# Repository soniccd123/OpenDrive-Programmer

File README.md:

# OpenDrive-Programmer
A open hardware USB programmer for the OpenDrive flashcart

# Other projects of the same family
- OpenDrive Genesis: https://github.com/soniccd123/OpenDrive-Genesis
- OpenDrive Programmer firmware: https://github.com/soniccd123/OpenDrive-Programmer-firmware
- OpenDrive Editor: https://github.com/soniccd123/OpenDrive-Editor

# What can it do?
- Read or write OpenDrive flashcarts Flash memory and FeRAM,
- Backup commercial cartridges
- Backup and restore commercial cartridges save games

# Why?
Created this from my old project with repros, as challenge and for personal use. Decided to share the project for other to use and learn. Hope it is useful to somebody!

# Why two boards?
This is just and option for those who are not so skilled with a soldering iron. The design contained in the Bluepill folders can use both a standart BluePill development module or be built as a standalone unit. When using a BluePill, not so many components are necessary and almost any SMD component is needed to be soldered (just the two 74LVC245). The design in the Standalone folder is the one that i've been using and its been tested, should be exactly equal to the BluePill one, it just don't have the solder points for the headers needed to connect the BluePill.

# How to use
Assemble the PCB, all the files needed for producing the PCB and Bill of Materials are available here. After assembling connect a STLINK to the STLINK port and write the firmware (available here: https://github.com/soniccd123/OpenDrive-Programmer-firmware). After that it is ready to be connected to a PC, it will be shown as a serial port. Connect to it using the OpenDrive Editor software and happy playing.

# Documentation
- Programmer Technical documentation, a constant work, sugestions are welcome:https://docs.google.com/document/d/e/2PACX-1vRtMwSrP43Q_9yeqR024jhnHt7tN-bjPW5AL-o--7ggXnXnSzmwVzF4QqODWmXAdS4KnoAx6XXx5pVw/pub
- MX29L3211 Datasheet: http://www.wolfgangrobel.de/electronics/datasheets/eprom/MX29L3211.pdf
- FM1808 Datasheet: https://datasheet.octopart.com/FM1808-70-PG-Ramtron-datasheet-8328945.pdf
- 74LVC8T245 Datasheet: https://assets.nexperia.com/documents/data-sheet/74LVC_LVCH8T245.pdf

# Troubleshooting
Most of the problems I had were related to bad solder joints, check and recheck your solder joints, specially the STM32 joints, lots of instabilities that I had were caused by falty contacts with solder.

# Disclaimer
I'm not a professional hardware engineer, while this programmer was designed to be the safest possible to your flashcart, I'm not responsible for any damages done if used or built wrong. Also, revise the design always before building the PCB, I'm a amateur human and errors may have been commited. It you spot anything, hit me with a message and I will happily fix that. Also, any sugestions are welcome!

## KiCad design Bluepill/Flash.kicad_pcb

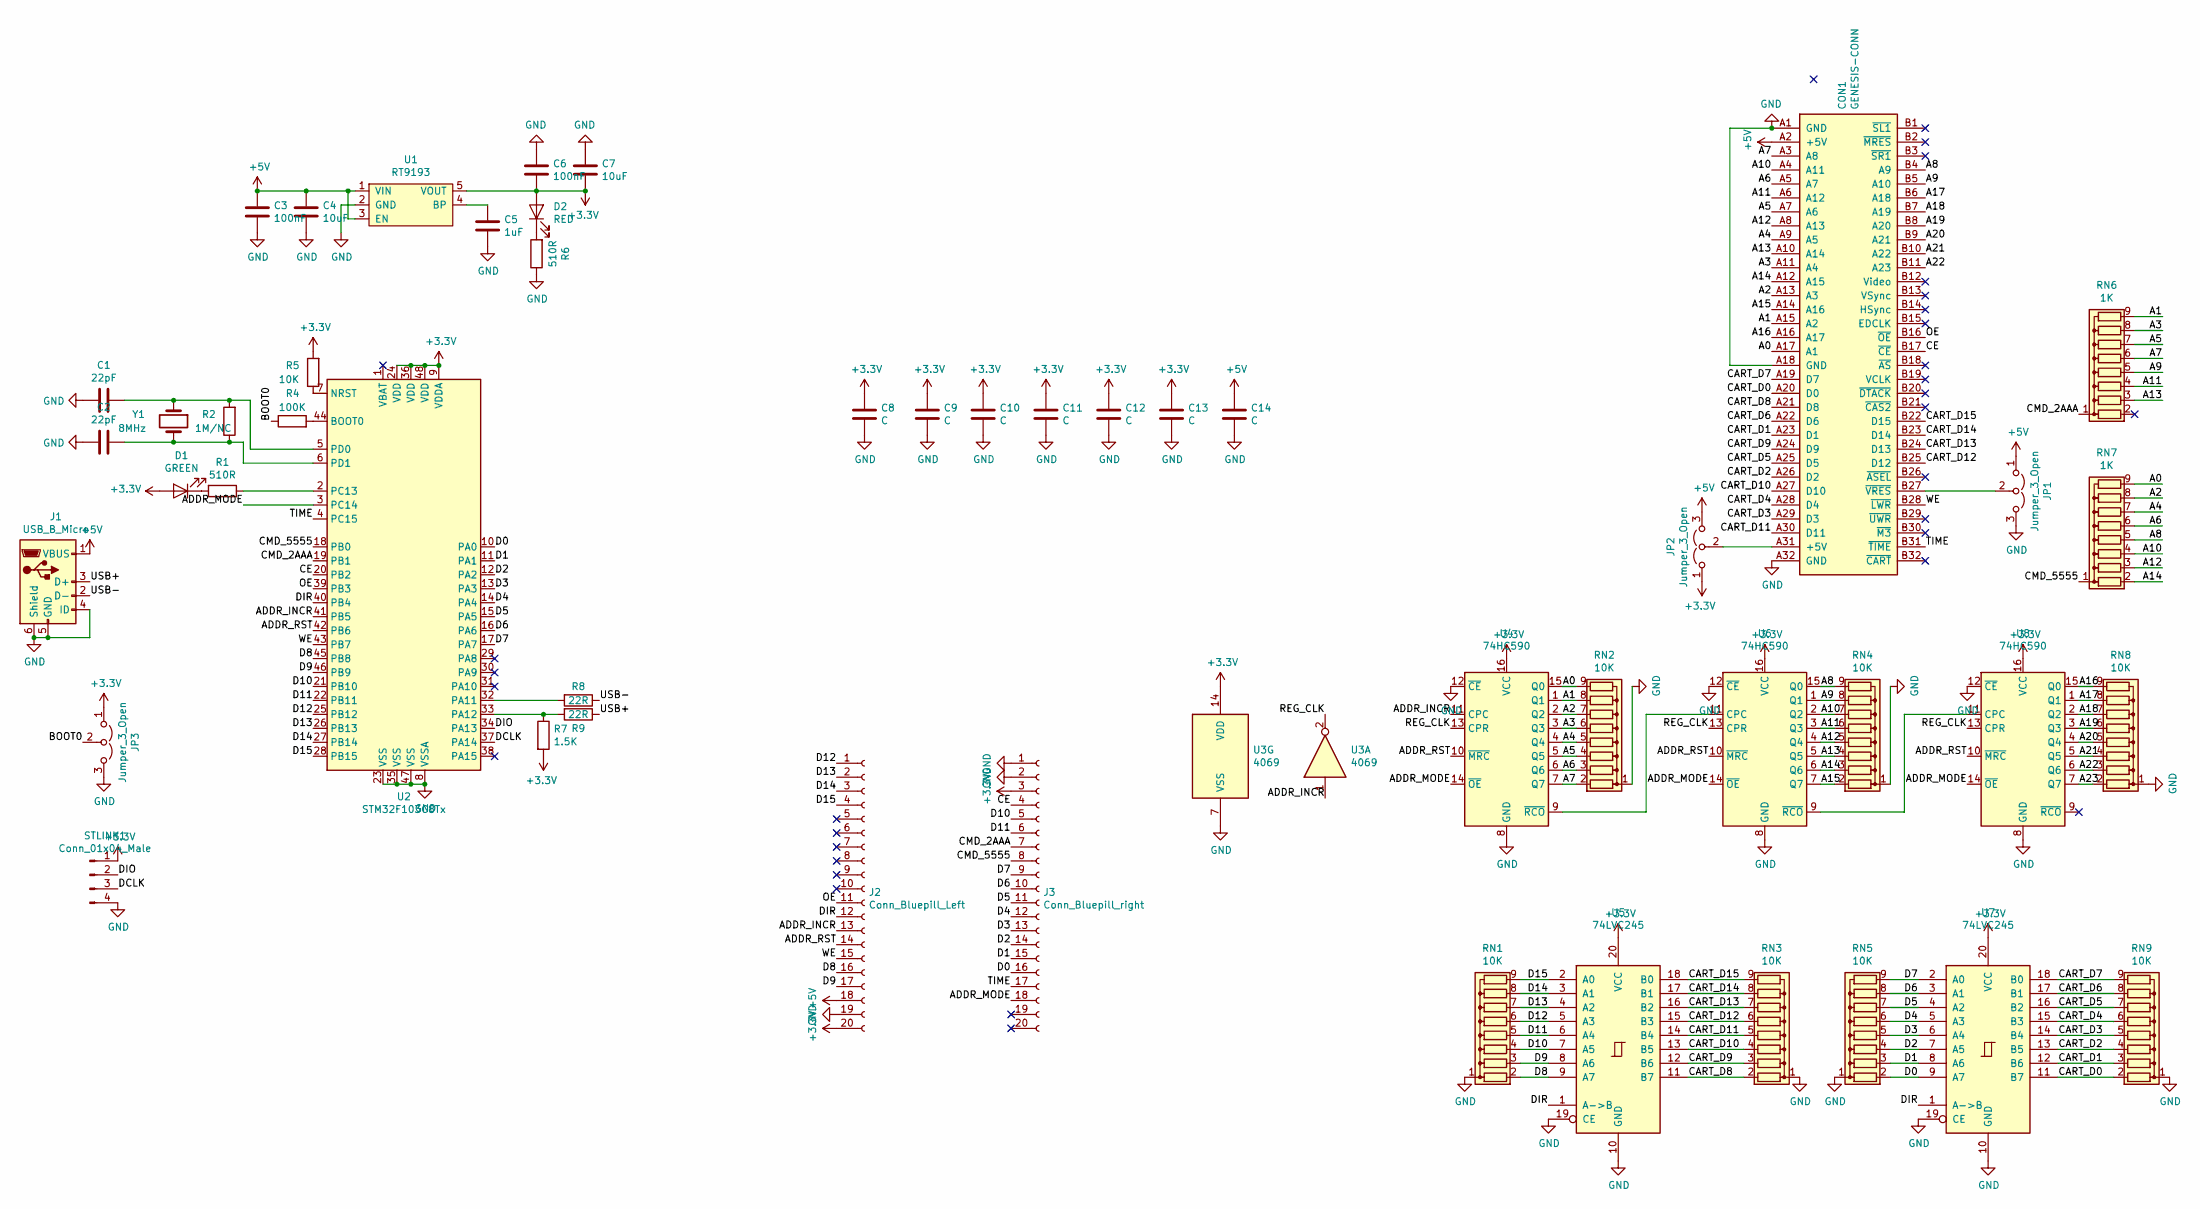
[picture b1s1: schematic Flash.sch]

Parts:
C1, C2: 22pF; C_0805_2012Metric_Pad1.15x1.40mm_HandSolder
C3, C6: 100nF; C_0805_2012Metric_Pad1.15x1.40mm_HandSolder
C4, C7: 10uF; C_0805_2012Metric_Pad1.15x1.40mm_HandSolder
C5: 1uF; C_0805_2012Metric_Pad1.15x1.40mm_HandSolder
C8, C9, C10, C11, C12, C13, C14: C; PinHeader_1x02_P2.54mm_Vertical
CON1: GENESIS-CONN; Digikey 1761469-1-ND
D1: GREEN; LED_D3.0mm
D2: RED; LED_D3.0mm
J1: USB_B_Micro; USB_Micro-B_Molex-105017-0001
J2: Conn_Bluepill_Left; PinSocket_1x20_P2.54mm_Vertical
J3: Conn_Bluepill_right; PinSocket_1x20_P2.54mm_Vertical
JP1, JP2, JP3: Jumper_3_Open; PinHeader_1x03_P2.54mm_Vertical
R1, R6: 510R; R_0805_2012Metric_Pad1.15x1.40mm_HandSolder
R2: 1M/NC; R_0805_2012Metric_Pad1.15x1.40mm_HandSolder
R4: 100K; R_0805_2012Metric_Pad1.15x1.40mm_HandSolder
R5: 10K; R_0805_2012Metric_Pad1.15x1.40mm_HandSolder
R7: 1.5K; R_0805_2012Metric_Pad1.15x1.40mm_HandSolder
R8, R9: 22R; R_0805_2012Metric_Pad1.15x1.40mm_HandSolder
RN1, RN2, RN3, RN4, RN5, RN8, RN9: 10K; R_Array_SIP9
RN6, RN7: 1K; R_Array_SIP9
STLINK1: Conn_01x04_Male; PinHeader_1x04_P2.54mm_Vertical
U1: RT9193; SOT-23-5_HandSoldering
U2: STM32F103C8Tx; LQFP-48_7x7mm_P0.5mm
U3: 4069; DIP-14_W7.62mm
U4, U6, U8: 74HC590; DIP-16_W7.62mm
U5, U7: 74LVC245; TSSOP-20_4.4x6.5mm_P0.65mm
Y1: 8MHz; Crystal_HC49-U_Vertical

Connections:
+3V3: C6.2, C7.2, C8.1, C9.1, C10.1, C11.1, C12.1, C13.1, D1.2 (A), D2.2 (A), J2.20, J3.3, JP2.1 (A), JP3.1 (A), R5.2, R7.2, STLINK1.1, U1.5 (VOUT), U2.9 (VDDA), U2.24 (VDD), U2.36 (VDD), U2.48 (VDD), U3.14 (VDD), U4.16 (VCC), U5.20 (VCC), U6.16 (VCC), U7.20 (VCC), U8.16 (VCC)
+5V: C3.1, C4.1, C14.1, CON1.A2 (+5V), J1.1 (VBUS), J2.18, JP1.1 (A), JP2.3 (B), U1.1 (VIN), U1.3 (EN)
/A0: CON1.A17 (A1), RN2.9 (R8), RN7.9 (R8), U4.15 (Q0)
/A1: CON1.A15 (A2), RN2.8 (R7), RN6.9 (R8), U4.1 (Q1)
/A2: CON1.A13 (A3), RN2.7 (R6), RN7.8 (R7), U4.2 (Q2)
/A3: CON1.A11 (A4), RN2.6 (R5), RN6.8 (R7), U4.3 (Q3)
/A4: CON1.A9 (A5), RN2.5 (R4), RN7.7 (R6), U4.4 (Q4)
/A5: CON1.A7 (A6), RN2.4 (R3), RN6.7 (R6), U4.5 (Q5)
/A6: CON1.A5 (A7), RN2.3 (R2), RN7.6 (R5), U4.6 (Q6)
/A7: CON1.A3 (A8), RN2.2 (R1), RN6.6 (R5), U4.7 (Q7)
/A8: CON1.B4 (A9), RN4.9 (R8), RN7.5 (R4), U6.15 (Q0)
/A9: CON1.B5 (A10), RN4.8 (R7), RN6.5 (R4), U6.1 (Q1)
/A10: CON1.A4 (A11), RN4.7 (R6), RN7.4 (R3), U6.2 (Q2)
/A11: CON1.A6 (A12), RN4.6 (R5), RN6.4 (R3), U6.3 (Q3)
/A12: CON1.A8 (A13), RN4.5 (R4), RN7.3 (R2), U6.4 (Q4)
/A13: CON1.A10 (A14), RN4.4 (R3), RN6.3 (R2), U6.5 (Q5)
/A14: CON1.A12 (A15), RN4.3 (R2), RN7.2 (R1), U6.6 (Q6)
/A15: CON1.A14 (A16), RN4.2 (R1), U6.7 (Q7)
/A16: CON1.A16 (A17), RN8.9 (R8), U8.15 (Q0)
/A17: CON1.B6 (A18), RN8.8 (R7), U8.1 (Q1)
/A18: CON1.B7 (A19), RN8.7 (R6), U8.2 (Q2)
/A19: CON1.B8 (A20), RN8.6 (R5), U8.3 (Q3)
/A20: CON1.B9 (A21), RN8.5 (R4), U8.4 (Q4)
/A21: CON1.B10 (A22), RN8.4 (R3), U8.5 (Q5)
/A22: CON1.B11 (A23), RN8.3 (R2), U8.6 (Q6)
/A23: RN8.2 (R1), U8.7 (Q7)
/ADDR_INCR: J2.13, U2.41 (PB5), U3.1, U4.11 (CPC)
/ADDR_MODE: J3.18, U2.3 (PC14), U4.14 (~OE), U6.14 (~OE), U8.14 (~OE)
/ADDR_RST: J2.14, U2.42 (PB6), U4.10 (~MRC), U6.10 (~MRC), U8.10 (~MRC)
/BOOT0: JP3.2 (C), R4.1
/CART_D0: CON1.A20 (D0), RN9.2 (R1), U7.11 (B7)
/CART_D1: CON1.A23 (D1), RN9.3 (R2), U7.12 (B6)
/CART_D2: CON1.A26 (D2), RN9.4 (R3), U7.13 (B5)
/CART_D3: CON1.A29 (D3), RN9.5 (R4), U7.14 (B4)
/CART_D4: CON1.A28 (D4), RN9.6 (R5), U7.15 (B3)
/CART_D5: CON1.A25 (D5), RN9.7 (R6), U7.16 (B2)
/CART_D6: CON1.A22 (D6), RN9.8 (R7), U7.17 (B1)
/CART_D7: CON1.A19 (D7), RN9.9 (R8), U7.18 (B0)
/CART_D8: CON1.A21 (D8), RN3.2 (R1), U5.11 (B7)
/CART_D9: CON1.A24 (D9), RN3.3 (R2), U5.12 (B6)
/CART_D10: CON1.A27 (D10), RN3.4 (R3), U5.13 (B5)
/CART_D11: CON1.A30 (D11), RN3.5 (R4), U5.14 (B4)
/CART_D12: CON1.B25 (D12), RN3.6 (R5), U5.15 (B3)
/CART_D13: CON1.B24 (D13), RN3.7 (R6), U5.16 (B2)
/CART_D14: CON1.B23 (D14), RN3.8 (R7), U5.17 (B1)
/CART_D15: CON1.B22 (D15), RN3.9 (R8), U5.18 (B0)
/CE: CON1.B17 (~CE), J3.4, U2.20 (PB2)
/CMD_2AAA: J3.7, RN6.1 (common), U2.19 (PB1)
/CMD_5555: J3.8, RN7.1 (common), U2.18 (PB0)
/D0: J3.16, RN5.2 (R1), U2.10 (PA0), U7.9 (A7)
/D1: J3.15, RN5.3 (R2), U2.11 (PA1), U7.8 (A6)
/D2: J3.14, RN5.4 (R3), U2.12 (PA2), U7.7 (A5)
/D3: J3.13, RN5.5 (R4), U2.13 (PA3), U7.6 (A4)
/D4: J3.12, RN5.6 (R5), U2.14 (PA4), U7.5 (A3)
/D5: J3.11, RN5.7 (R6), U2.15 (PA5), U7.4 (A2)
/D6: J3.10, RN5.8 (R7), U2.16 (PA6), U7.3 (A1)
/D7: J3.9, RN5.9 (R8), U2.17 (PA7), U7.2 (A0)
/D8: J2.16, RN1.2 (R1), U2.45 (PB8), U5.9 (A7)
/D9: J2.17, RN1.3 (R2), U2.46 (PB9), U5.8 (A6)
/D10: J3.5, RN1.4 (R3), U2.21 (PB10), U5.7 (A5)
/D11: J3.6, RN1.5 (R4), U2.22 (PB11), U5.6 (A4)
/D12: J2.1, RN1.6 (R5), U2.25 (PB12), U5.5 (A3)
/D13: J2.2, RN1.7 (R6), U2.26 (PB13), U5.4 (A2)
/D14: J2.3, RN1.8 (R7), U2.27 (PB14), U5.3 (A1)
/D15: J2.4, RN1.9 (R8), U2.28 (PB15), U5.2 (A0)
/DCLK: STLINK1.3, U2.37 (PA14)
/DIO: STLINK1.2, U2.34 (PA13)
/DIR: J2.12, U2.40 (PB4), U5.1 (A->B), U7.1 (A->B)
/OE: CON1.B16 (~OE), J2.11, U2.39 (PB3)
/REG_CLK: U3.2, U4.13 (CPR), U6.13 (CPR), U8.13 (CPR)
/TIME: CON1.B31 (~TIME), J3.17, U2.4 (PC15)
/USB+: J1.3 (D+), R9.1
/USB-: J1.2 (D-), R8.1
/WE: CON1.B28 (~LWR), J2.15, U2.43 (PB7)
GND: C1.2, C2.2, C3.2, C4.2, C5.2, C6.1, C7.1, C8.2, C9.2, C10.2, C11.2, C12.2, C13.2, C14.2, CON1.A1 (GND), CON1.A18 (GND), CON1.A32 (GND), J1.4 (ID), J1.5 (GND), J1.6 (Shield), J2.19, J3.1, J3.2, JP1.3 (B), JP3.3 (B), R6.1, RN1.1 (common), RN2.1 (common), RN3.1 (common), RN4.1 (common), RN5.1 (common), RN8.1 (common), RN9.1 (common), STLINK1.4, U1.2 (GND), U2.8 (VSSA), U2.23 (VSS), U2.35 (VSS), U2.47 (VSS), U3.7 (VSS), U4.8 (GND), U4.12 (~CE), U5.10 (GND), U5.19 (CE), U6.8 (GND), U6.12 (~CE), U7.10 (GND), U7.19 (CE), U8.8 (GND), U8.12 (~CE)
unnamed: C1.1, R2.2, U2.5 (PD0), Y1.1
unnamed: C2.1, R2.1, U2.6 (PD1), Y1.2
unnamed: C5.1, U1.4 (BP)
unnamed: CON1.A31 (+5V), JP2.2 (C)
unnamed: CON1.B27 (~VRES), JP1.2 (C)
unnamed: D1.1 (K), R1.2
unnamed: D2.1 (K), R6.2
unnamed: R1.1, U2.2 (PC13)
unnamed: R4.2, U2.44 (BOOT0)
unnamed: R5.1, U2.7 (NRST)
unnamed: R7.1, R9.2, U2.33 (PA12)
unnamed: R8.2, U2.32 (PA11)
unnamed: U4.9 (~RCO), U6.11 (CPC)
unnamed: U6.9 (~RCO), U8.11 (CPC)

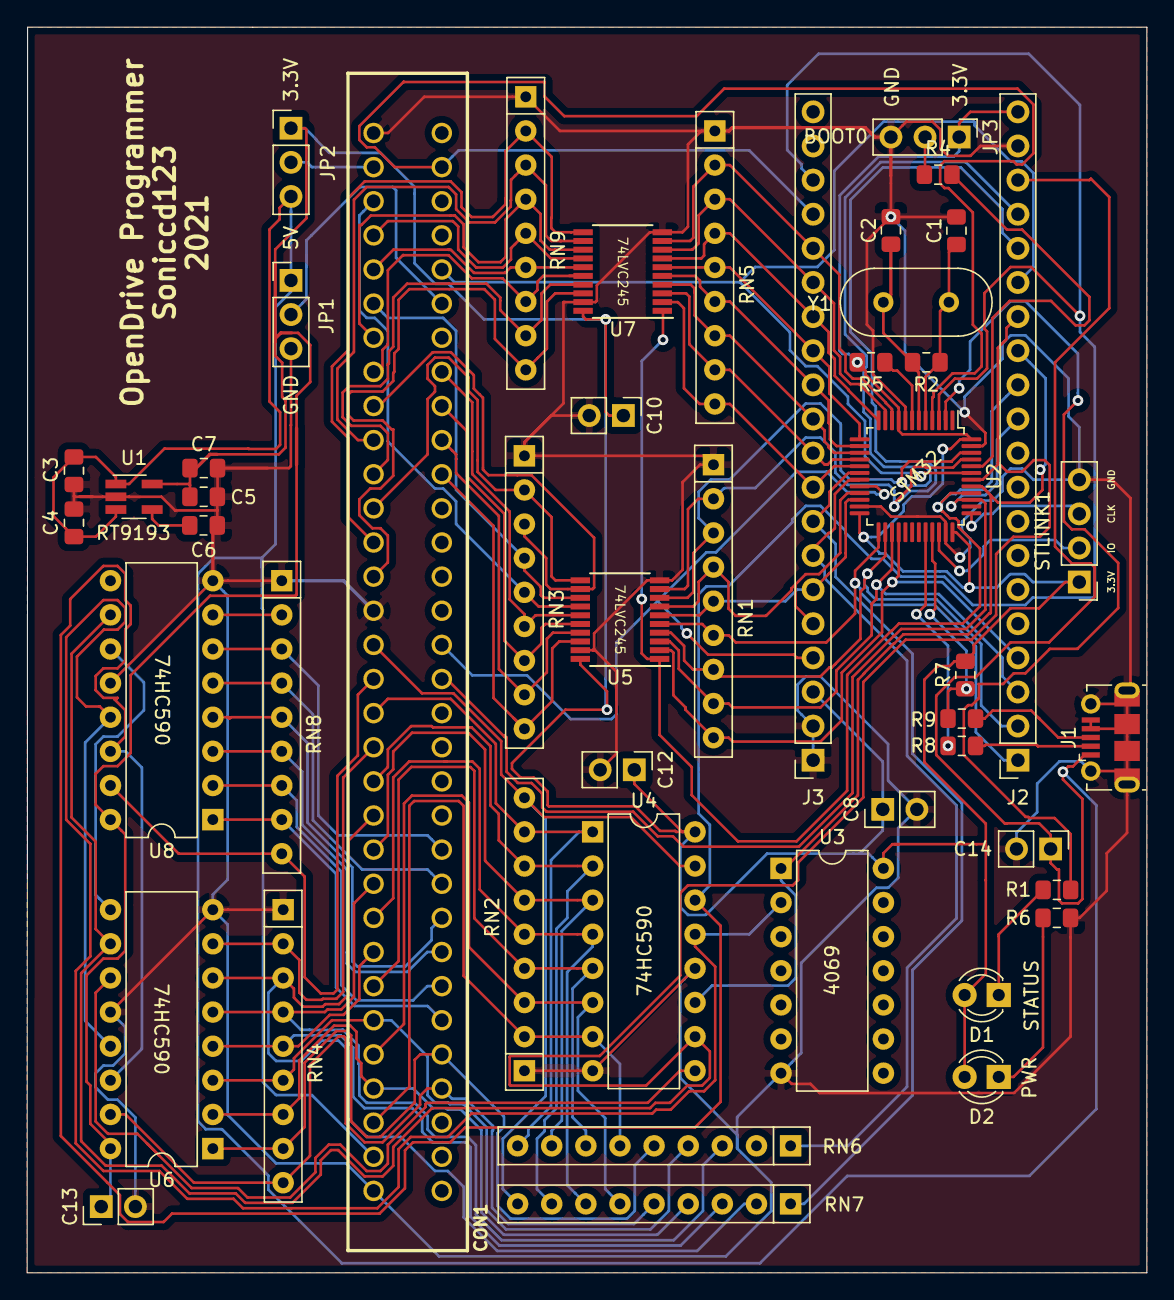
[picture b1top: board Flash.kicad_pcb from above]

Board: 2 copper layers, 83.3 x 92.7 mm, 48 parts (0 on the bottom side), 89 nets.

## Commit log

2021-02-28 Small silkscreen changes
2021-03-03 Connected A22 and A23 on the cart connector for SNES support
